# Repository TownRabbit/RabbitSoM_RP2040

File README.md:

# RabbitSoM_RP2040

## Overview
Qiita見て

## License

The hardware design files in this repository are licensed under the CERN Open Hardware Licence Version 2 - Permissive (CERN-OHL-P-2.0).

You are free to use, study, modify, manufacture, and commercially distribute products based on these designs, subject to the terms of the license.

Publishing modified design files is not generally required when distributing products based on these designs. Redistribution of the design files themselves remains subject to the license terms.

See [LICENSE](LICENSE) for the full license text.

Third-party components and materials may be subject to separate licenses.

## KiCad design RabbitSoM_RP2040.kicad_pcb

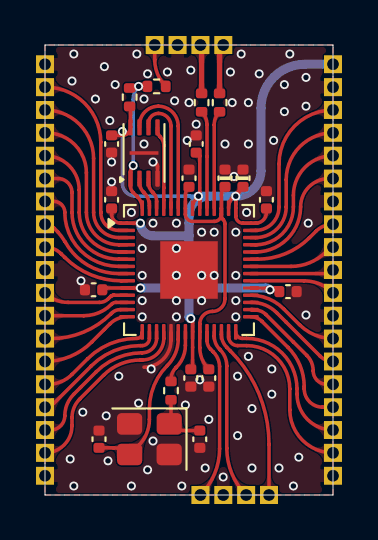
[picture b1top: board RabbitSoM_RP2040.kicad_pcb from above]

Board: 2 copper layers, 16.0 x 25.0 mm, 25 parts (0 on the bottom side), 50 nets.

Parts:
C1, C2: 15pF/30pF; C_0402_1005Metric
C3, C13: 1µ; C_0402_1005Metric
C4, C5, C6, C7, C8, C9, C10, C11, C12: 100n; C_0402_1005Metric
J1, J2: Conn_01x19; PinHeader_1x19_P1.27mm_Vertical
J3, J4: Conn_01x04; PinHeader_1x04_P1.27mm_Vertical
R1, R2: 22; R_0402_1005Metric
R3, R5: 1k; R_0402_1005Metric
R4: 10k; R_0402_1005Metric
U1: W25Q16JVUXIQ; Winbond_USON-8-1EP_3x2mm_P0.5mm_EP0.2x1.6mm
U2: RP2040; QFN-56-1EP_7x7mm_P0.4mm_EP3.2x3.2mm
Y1: 12MHz; Crystal_SMD_3225-4Pin_3.2x2.5mm

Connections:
0: J1.2, U2.2 (GPIO0)
1: J1.3, U2.3 (GPIO1)
2: J1.4, U2.4 (GPIO2)
3: J1.5, U2.5 (GPIO3)
4: J1.6, U2.6 (GPIO4)
5: J1.7, U2.7 (GPIO5)
6: J1.8, U2.8 (GPIO6)
7: J1.9, U2.9 (GPIO7)
8: J1.11, U2.11 (GPIO8)
9: J1.12, U2.12 (GPIO9)
10: J1.13, U2.13 (GPIO10)
11: J1.14, U2.14 (GPIO11)
12: J1.15, U2.15 (GPIO12)
13: J1.16, U2.16 (GPIO13)
14: J1.17, U2.17 (GPIO14)
15: J1.18, U2.18 (GPIO15)
16: J2.2, U2.27 (GPIO16)
17: J2.3, U2.28 (GPIO17)
18: J2.4, U2.29 (GPIO18)
19: J2.5, U2.30 (GPIO19)
20: J2.6, U2.31 (GPIO20)
21: J2.7, U2.32 (GPIO21)
22: J2.9, U2.34 (GPIO22)
23: J2.10, U2.35 (GPIO23)
24: J2.11, U2.36 (GPIO24)
25: J2.12, U2.37 (GPIO25)
+3.3V: C6.1, C7.1, C8.1, C9.1, C10.1, C11.1, C12.1, C13.1, J2.19, R4.1, U1.8 (VCC), U2.1 (IOVDD), U2.10 (IOVDD), U2.22 (IOVDD), U2.33 (IOVDD), U2.42 (IOVDD), U2.43 (ADC_AVDD), U2.44 (VREG_IN), U2.48 (USB_VDD), U2.49 (IOVDD)
/RP2040/1.1V: C3.1, C4.1, C5.1, U2.23 (DVDD), U2.45 (VREG_VOUT), U2.50 (DVDD)
/RP2040/RP2040_D+: R1.2, U2.47 (USB_DP)
/RP2040/RP2040_D-: R2.2, U2.46 (USB_DM)
A0: J2.14, U2.38 (GPIO26_ADC0)
A1: J2.15, U2.39 (GPIO27_ADC1)
A2: J2.16, U2.40 (GPIO28_ADC2)
A3: J2.17, U2.41 (GPIO29_ADC3)
BOOT: J3.4, R5.2
D+: J3.2, R1.1
D-: J3.1, R2.1
GND: C1.2, C2.2, C3.2, C4.2, C5.2, C6.2, C7.2, C8.2, C9.2, C10.2, C11.2, C12.2, C13.2, J1.1, J1.10, J1.19, J2.1, J2.8, J2.13, J2.18, J3.3, J4.2, U1.4 (GND), U1.9 (GND), U2.19 (TESTEN), U2.57 (GND), Y1.2, Y1.4
unnamed: C2.1, R3.1, Y1.1
unnamed: U1.6 (CLK), U2.52 (QSPI_SCLK)
unnamed: U1.5 (DI/IO_{0}), U2.53 (QSPI_SD0)
unnamed: U1.2 (DO/IO_{1}), U2.55 (QSPI_SD1)
unnamed: R4.2, R5.1, U1.1 (~CS), U2.56 (QSPI_SS)
unnamed: U1.7 (~HOLD/~RESET/IO_{3}), U2.51 (QSPI_SD3)
unnamed: U1.3 (~WP/IO_{2}), U2.54 (QSPI_SD2)
unnamed: C1.1, U2.20 (XIN), Y1.3
unnamed: R3.2, U2.21 (XOUT)
RUN: J4.4, U2.26 (RUN)
SWCLK: J4.1, U2.24 (SWCLK)
SWDIO: J4.3, U2.25 (SWD)

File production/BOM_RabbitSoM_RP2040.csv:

Designator,Footprint,Quantity,Value,LCSC Part #
"C1, C2",0402,2,30p,C1570
"C10, C11, C12, C4, C5, C6, C7, C8, C9",0402,9,100n,C1525
"C13, C3",0402,2,1µ,C52923
"J1, J2",PinHeader_1x19_P1.27mm_Vertical,2,Conn_01x19,
"J3, J4",PinHeader_1x04_P1.27mm_Vertical,2,Conn_01x04,
"R1, R2",0402,2,22,C25092
"R3, R5",0402,2,1k,C11702
R4,0402,1,10k,C25744
U1,Winbond_USON-8-1EP_3x2mm_P0.5mm_EP0.2x1.6mm,1,W25Q16JVUXIQ,C2843335
U2,QFN-56-1EP_7x7mm_P0.4mm_EP3.2x3.2mm,1,RP2040,C2040
Y1,Crystal_SMD_3225-4Pin_3.2x2.5mm,1,12MHz,C9002
